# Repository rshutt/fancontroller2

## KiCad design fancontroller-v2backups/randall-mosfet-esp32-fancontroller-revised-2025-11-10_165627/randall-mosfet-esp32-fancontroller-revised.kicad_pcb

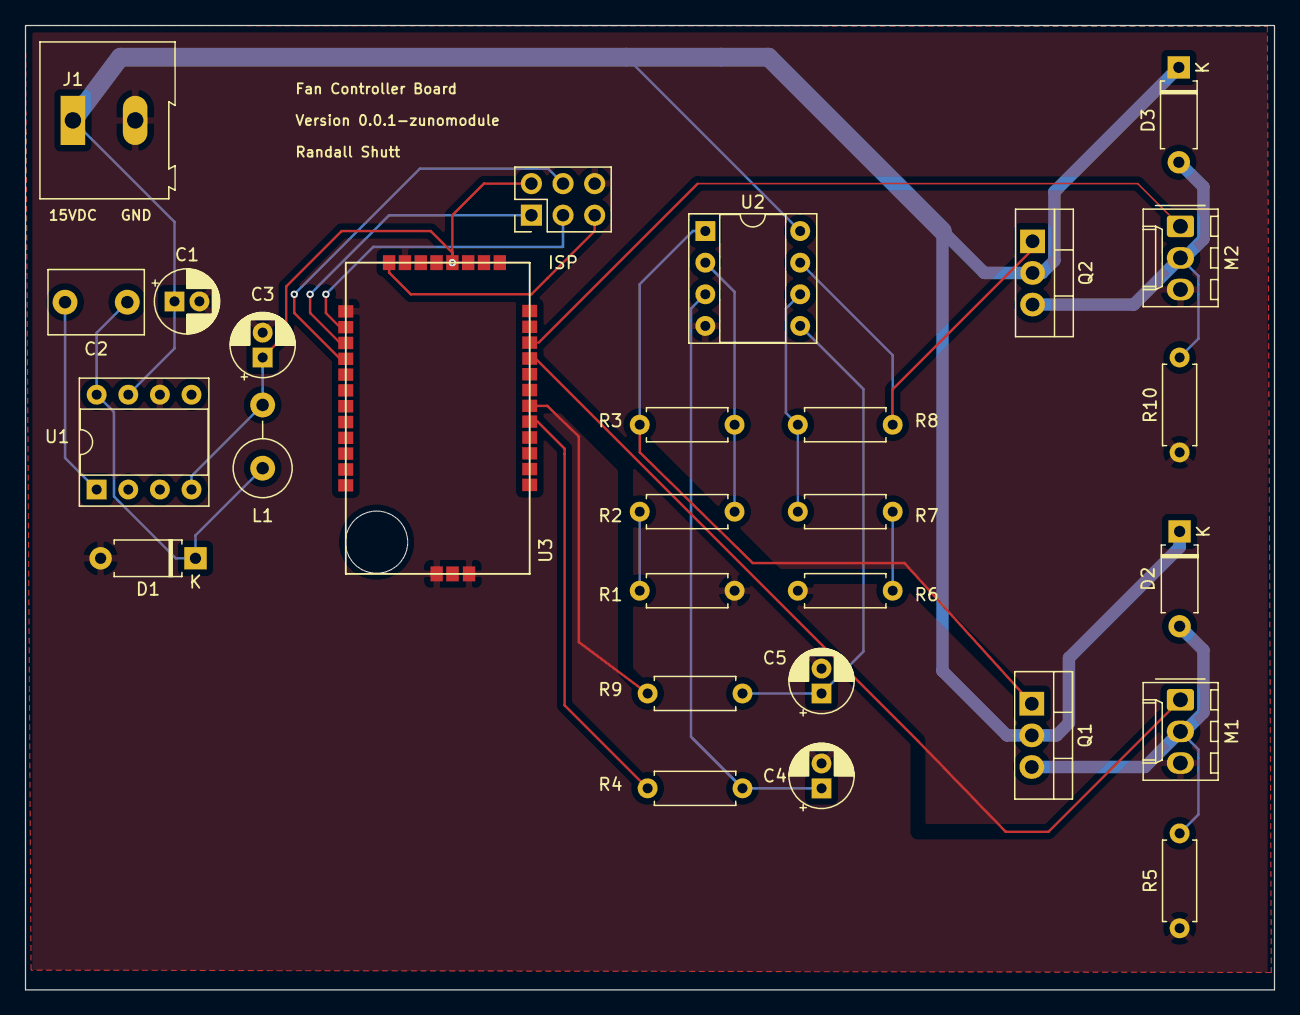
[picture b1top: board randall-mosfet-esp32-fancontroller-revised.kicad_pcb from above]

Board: 2 copper layers, 100.3 x 77.5 mm, 28 parts (0 on the bottom side), 23 nets.

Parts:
C1, C3, C4, C5: 100uF; CP_Radial_D5.0mm_P2.00mm
C2: 0.01uF; C_Disc_D7.5mm_W5.0mm_P5.00mm
D1: D_Schottky; D_A-405_P7.62mm_Horizontal
D2, D3: 1N1004; D_A-405_P7.62mm_Horizontal
ISP: AVR-ISP-6; PinHeader_2x03_P2.54mm_Vertical
J1: Power; TerminalBlock_Altech_AK300-2_P5.00mm
L1: 68uH; L_Axial_L14.0mm_D4.5mm_P5.08mm_Vertical_Fastron_LACC
M1, M2: Fan_3pin; Molex_KK-254_AE-6410-03A_1x03_P2.54mm_Vertical
Q1, Q2: TIP120; TO-220-3_Vertical
R1, R6: 390; R_Axial_DIN0207_L6.3mm_D2.5mm_P7.62mm_Horizontal
R2, R7: 3.9k; R_Axial_DIN0207_L6.3mm_D2.5mm_P7.62mm_Horizontal
R3, R8: 15k; R_Axial_DIN0207_L6.3mm_D2.5mm_P7.62mm_Horizontal
R4, R9: 330; R_Axial_DIN0207_L6.3mm_D2.5mm_P7.62mm_Horizontal
R5, R10: 46k; R_Axial_DIN0207_L6.3mm_D2.5mm_P7.62mm_Horizontal
U1: LM2674M-3.3; DIP-8_W7.62mm_Socket
U2: LM358; DIP-8_W7.62mm_Socket
U3: Z-Uno-Module; Z-UNO Module

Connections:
3V3DC: C3.1, ISP.2, L1.2, U1.4, U3.26
15VDC: C1.1, D2.1, D3.1, J1.1, Q1.2, Q2.2, U1.7, U2.8
GND: C1.2, C3.2, C4.2, C5.2, D1.2, ISP.6, J1.2, M1.3, M2.3, R1.2, R5.1, R6.2, R10.1, U1.6, U2.4, U3.29, U3.31, U3.32, U3.34
MISO: ISP.1, U3.1
MOSI: ISP.4, U3.2
unnamed: C2.1, D1.1, L1.1, U1.8
unnamed: C2.2, U1.1
unnamed: C4.1, R4.1, U2.3
unnamed: C5.1, R9.1, U2.5
unnamed: D2.2, M1.2, Q1.3, R5.2
unnamed: D3.2, M2.2, Q2.3, R10.2
unnamed: Q1.1, R3.1, U2.1
unnamed: Q2.1, R8.1, U2.7
unnamed: R1.1, R2.2
unnamed: R2.1, R3.2, U2.2
unnamed: R6.1, R7.2
unnamed: R7.1, R8.2, U2.6
PWM1: R4.2, U3.13
PWM2: R9.2, U3.14
RST: ISP.5, U3.30
SCK: ISP.3, U3.0
TACH1: M1.1, U3.17
TACH2: M2.1, U3.18

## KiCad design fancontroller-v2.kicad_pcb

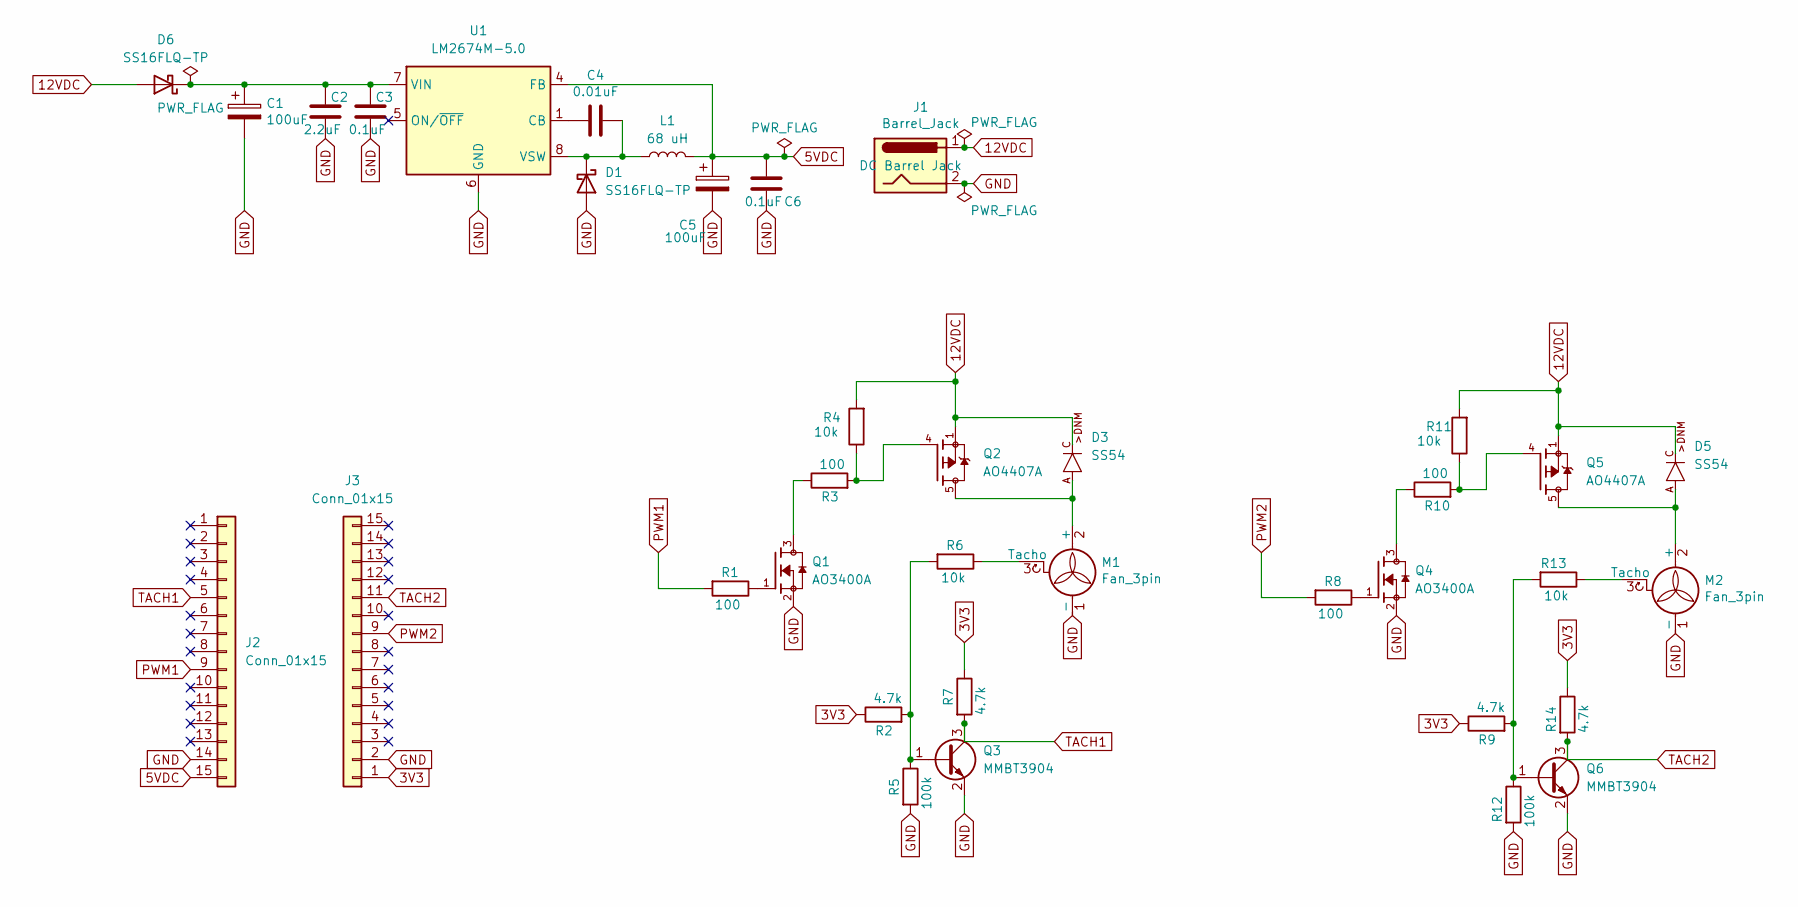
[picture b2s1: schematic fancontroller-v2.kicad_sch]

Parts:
C1, C5: 100uF; CP_Radial_D5.0mm_P2.00mm
C2: 2.2uF; C_0805_2012Metric
C3, C6: 0.1uF; C_0805_2012Metric
C4: 0.01uF; C_0603_1608Metric
D1, D6: SS16FLQ-TP; D_SMA
D3, D5: SS54; DO-214AC; MPN SS54
J1: Barrel_Jack; BarrelJack_CUI_PJ-063AH_Horizontal_CircularHoles
J2, J3: Conn_01x15; PinHeader_1x15_P2.54mm_Vertical
L1: 68 uH; L_7.3x7.3_H4.5
M1, M2: Fan_3pin; Molex_KK-254_AE-6410-03A_1x03_P2.54mm_Vertical
Q1, Q4: AO3400A; SOT-23; PARTREV L
Q2, Q5: AO4407A; SOIC127P600X175-8N; PARTREV I; DigiKey_Part_Number 785-1022-1-ND
Q3: MMBT3904; SOT-23
Q6: MMBT3904; SOT-23_Handsoldering
R1, R3, R8, R10: 100; R_0805_2012Metric_Pad1.20x1.40mm_HandSolder
R2, R7, R9, R14: 4.7k; R_0805_2012Metric_Pad1.20x1.40mm_HandSolder
R4, R6, R11, R13: 10k; R_0805_2012Metric_Pad1.20x1.40mm_HandSolder
R5, R12: 100k; R_0805_2012Metric_Pad1.20x1.40mm_HandSolder
U1: LM2674M-5.0; SOIC-8_3.9x4.9mm_P1.27mm

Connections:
3V3: J3.1, R2.1, R7.1, R9.1, R14.1
5VDC: C5.1, C6.1, J2.15, L1.2, U1.4 (FB)
12VDC: D3.C, D5.C, D6.2 (A), J1.1, Q2.1, Q2.2, Q2.3, Q5.1, Q5.2, Q5.3, R4.2, R11.2
GND: C1.2, C2.2, C3.2, C5.2, C6.2, D1.2 (A), J1.2, J2.14, J3.2, M1.1 (-), M2.1 (-), Q1.2, Q3.2 (E), Q4.2, Q6.2 (E), R5.2, R12.2, U1.6 (GND)
unnamed: C4.1, D1.1 (K), L1.1, U1.8 (VSW)
unnamed: C1.1, C2.1, C3.1, D6.1 (K), U1.7 (VIN)
unnamed: D3.A, M1.2 (+), Q2.5, Q2.6, Q2.7, Q2.8
unnamed: M1.3 (Tacho), R6.1
unnamed: D5.A, M2.2 (+), Q5.5, Q5.6, Q5.7, Q5.8
unnamed: M2.3 (Tacho), R13.1
unnamed: Q1.1, R1.1
unnamed: Q1.3, R3.1
unnamed: Q2.4, R3.2, R4.1
unnamed: Q3.1 (B), R2.2, R5.1, R6.2
unnamed: Q4.1, R8.1
unnamed: Q4.3, R10.1
unnamed: Q5.4, R10.2, R11.1
unnamed: Q6.1 (B), R9.2, R12.1, R13.2
unnamed: C4.2, U1.1 (CB)
PWM1: J2.9, R1.2
PWM2: J3.9, R8.2
TACH1: J2.5, Q3.3 (C), R7.2
TACH2: J3.11, Q6.3 (C), R14.2

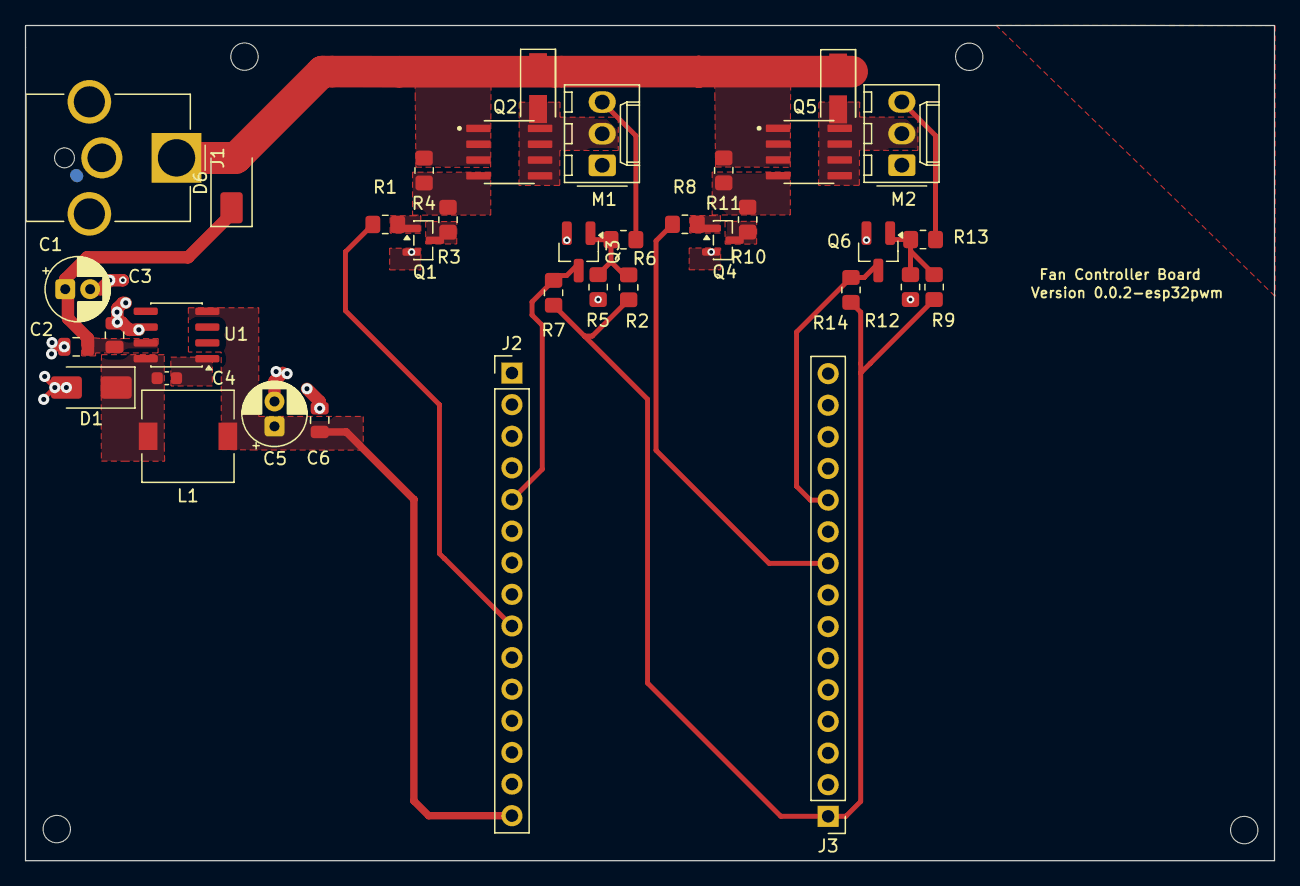
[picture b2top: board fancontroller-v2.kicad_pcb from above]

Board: 2 copper layers, 100.3 x 67.1 mm, 37 parts (0 on the bottom side), 23 nets.

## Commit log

2025-12-17 Upgraded to v2 alpha 1
2025-12-17 Adding the new pcb and sch files
2025-12-18 Doing some cleanup
2025-12-19 No Comment
